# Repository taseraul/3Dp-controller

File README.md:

# 3Dp-controller
Atmega2560 compatible 3d printer controller with integrated tmc2130 stepper drivers

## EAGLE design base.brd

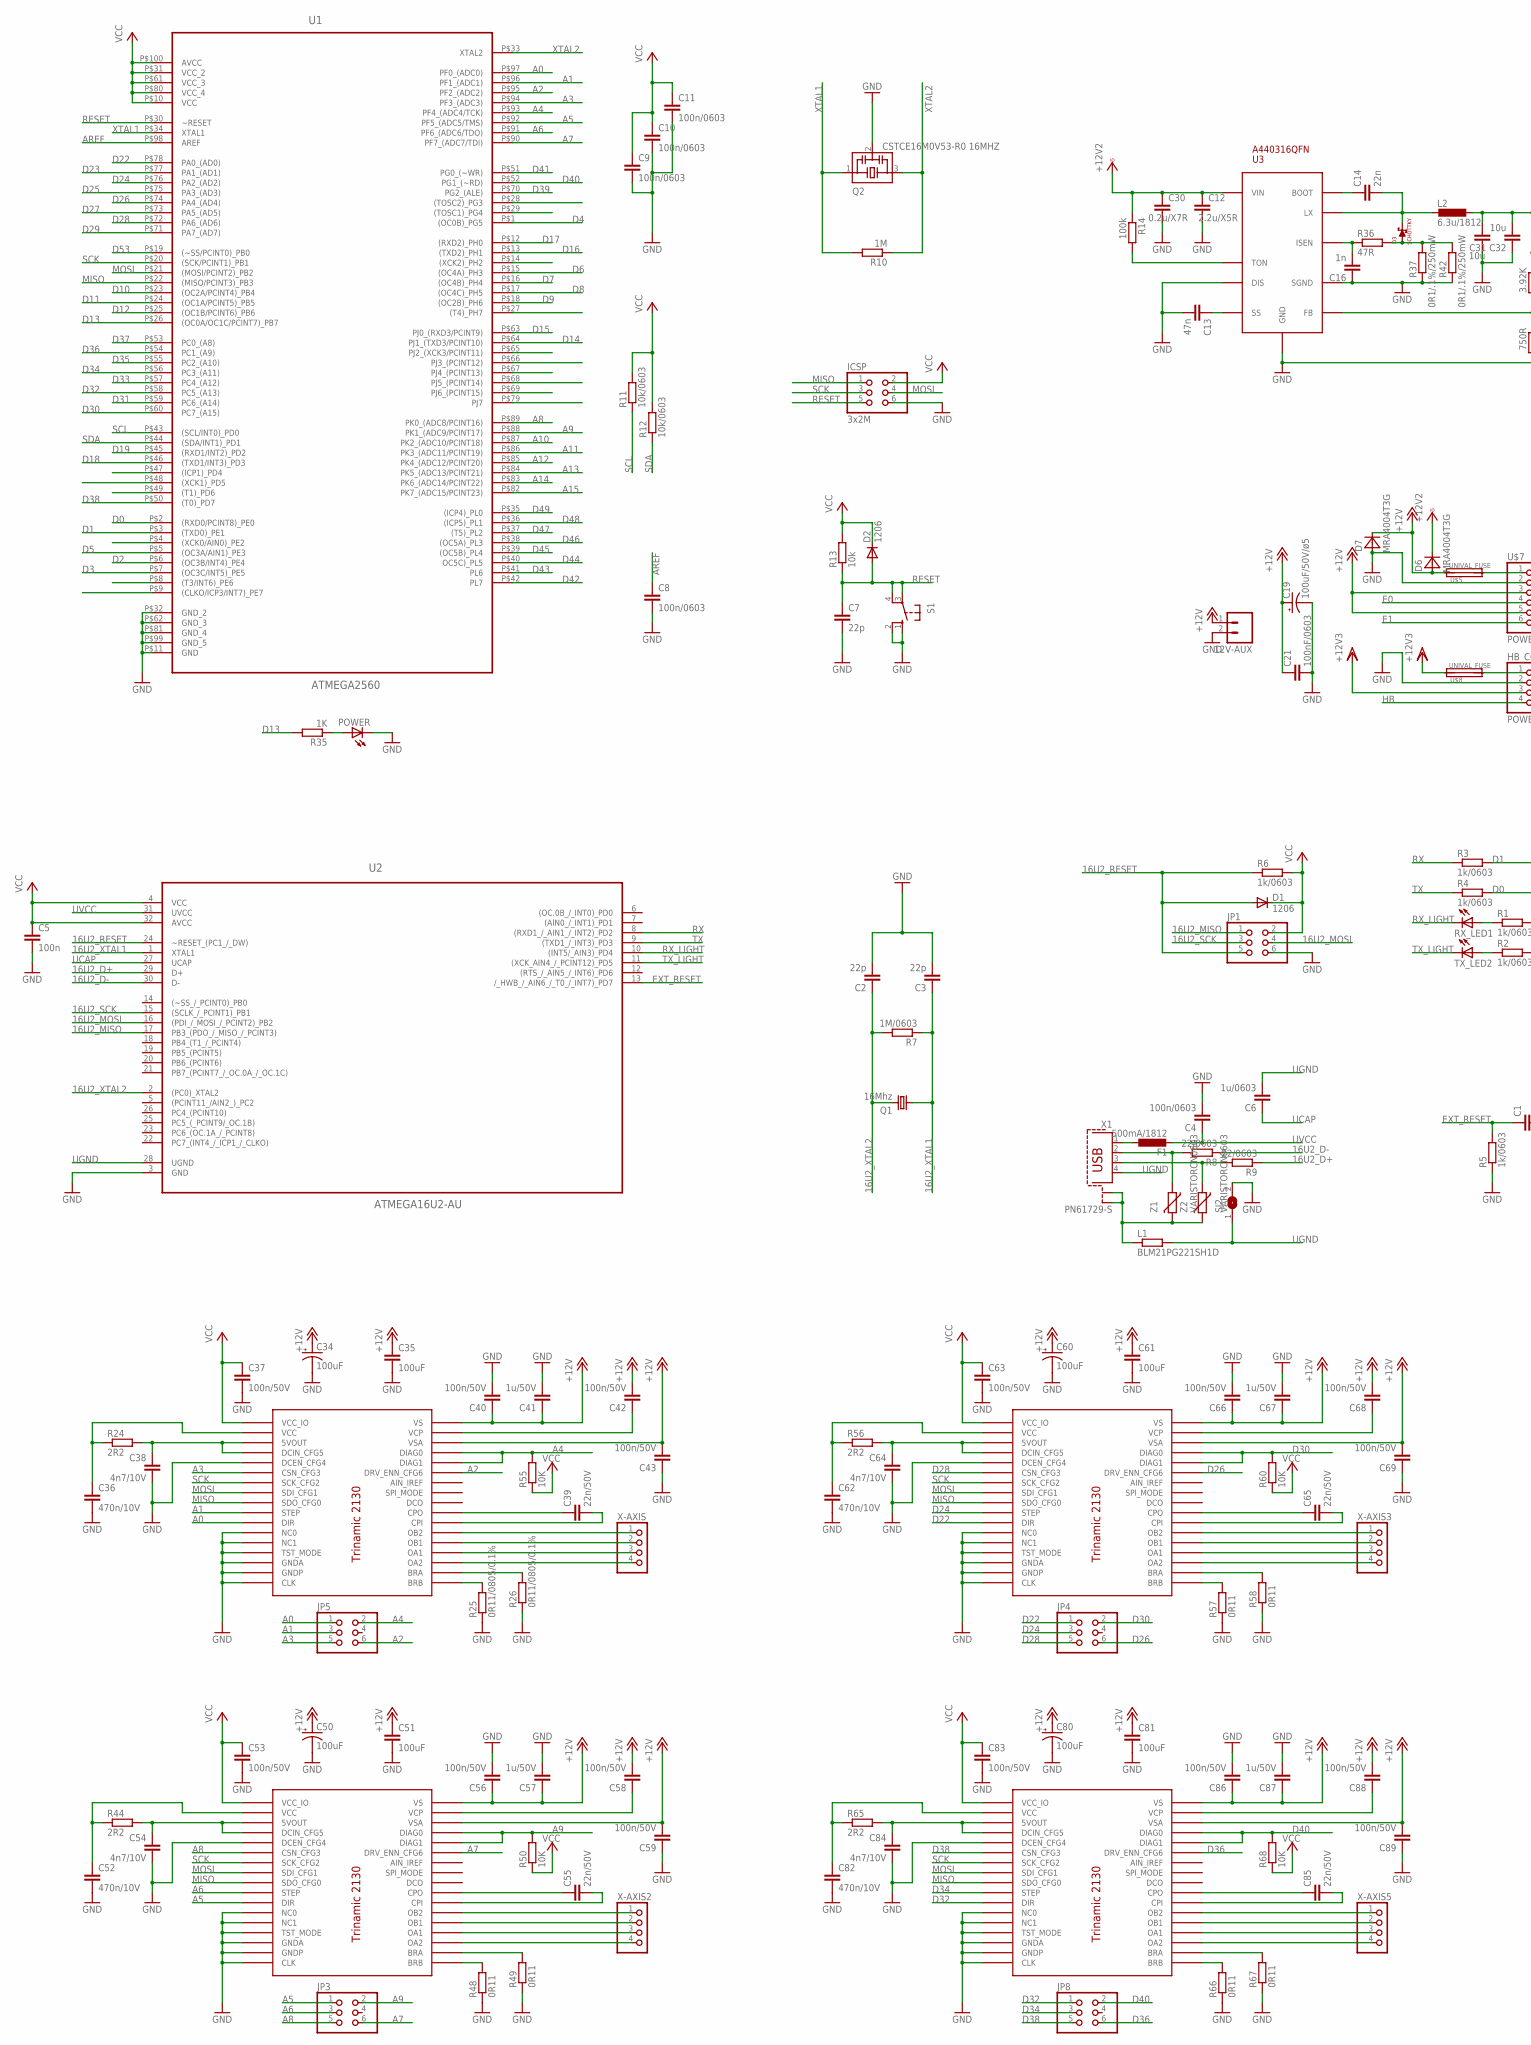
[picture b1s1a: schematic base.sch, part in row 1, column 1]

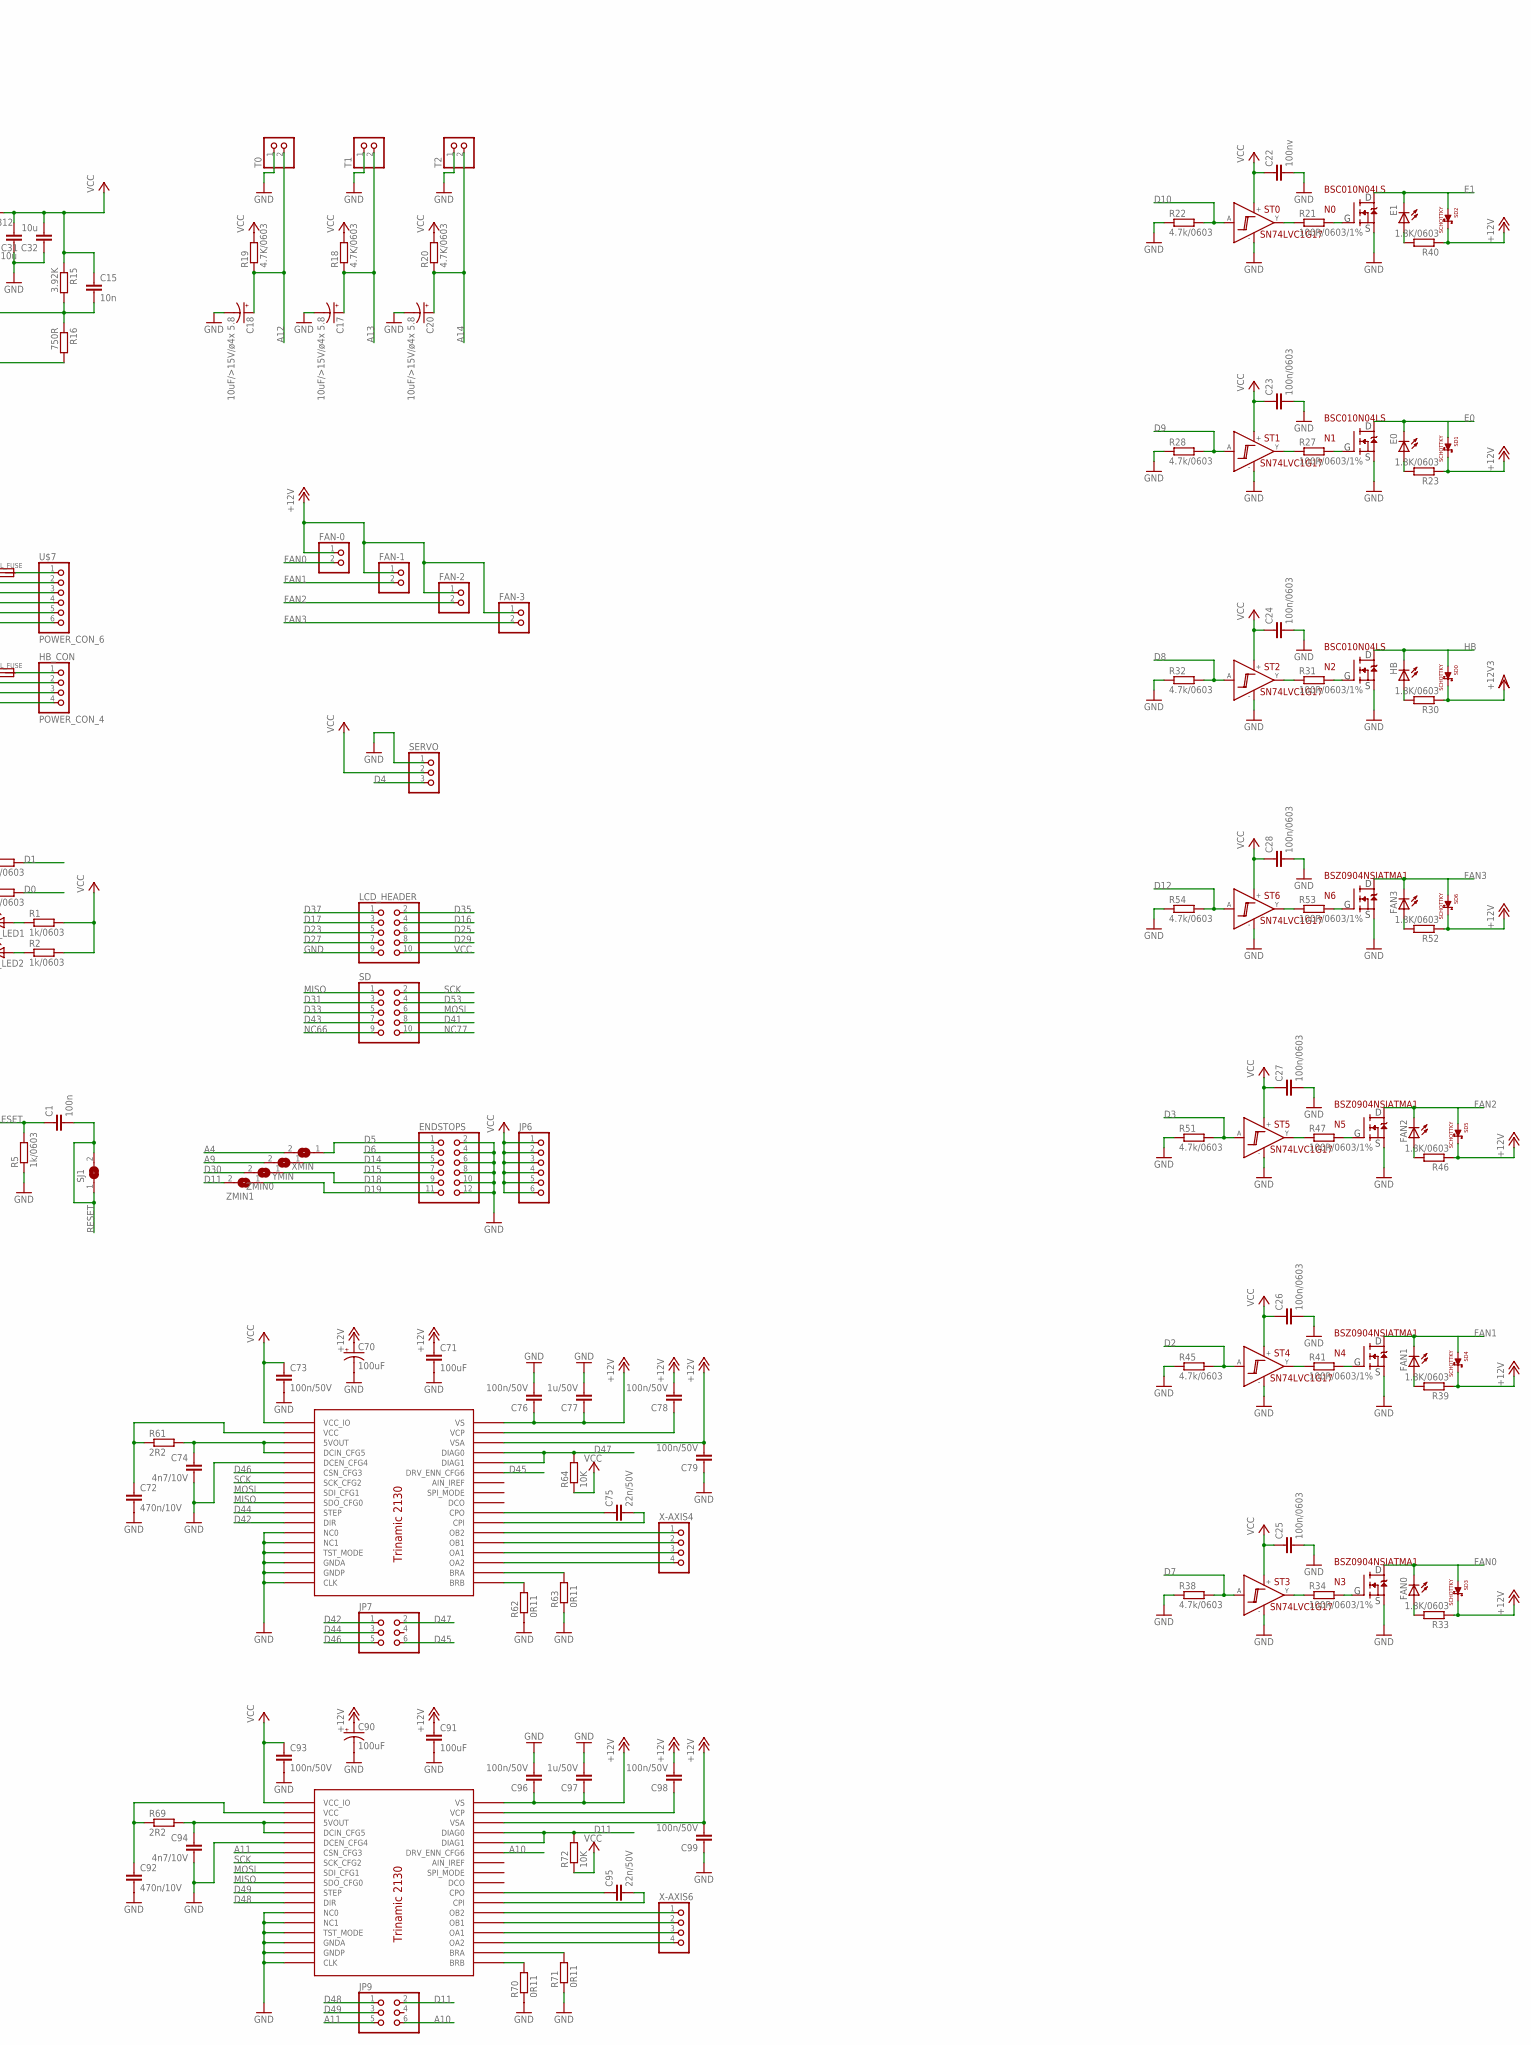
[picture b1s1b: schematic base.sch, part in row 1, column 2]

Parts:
12V-AUX: M02PTH; 1X02
C1, C5: 100n; C0603
C2, C3, C7: 22p; C0603
C4, C8, C9, C10, C11, C23, C24, C25, C26, C27, C28: 100n/0603; C0603
C6: 1u/0603; C0603
C12: 2.2u/X5R; C0805
C13: 47n; C0603
C14: 22n; C0603
C15: 10n; C0603
C16: 1n; C0603
C17, C18, C20: 10uF/>15V/ø4x 5.8; 153CLV-0405
C19: 100uF/50V/ø5; 153CLV-0605
C21: 100nF/0603; C0805
C22: 100nv; C0603
C30: 0.2u/X7R; C0603
C31, C32: 10u; C0603
C34, C50, C60, C70, C80, C90: 100uF; 153CLV-0605
C35, C51, C61, C71, C81, C91: 100uF; C0603
C36, C52, C62, C72, C82, C92: 470n/10V; C0402
C37, C40, C42, C43, C53, C56, C58, C59, C63, C66, C68, C69, C73, C76, C78, C79, C83, C86, C88, C89, C93, C96, C98, C99: 100n/50V; C0402
C38, C54, C64, C74, C84, C94: 4n7/10V; C0402
C39, C55, C65, C75, C85, C95: 22n/50V; C0402
C41, C57, C67, C77, C87, C97: 1u/50V; C0603
D1: 1206; MICROMELF-W
D2: 1206; MINIMELF
D3: SCHOTTKY; MICROSMP
D6, D7: MRA4004T3G; SMA
E0, E1: LEDCHIP-LED0805; CHIP-LED0805
ENDSTOPS: PINHD-2X6/90; 2X06/90
F1: 500mA/1812; L1812
FAN0, FAN1, FAN2, FAN3: LEDCHIP-LED0805; CHIP-LED0805
FAN-0, FAN-1, FAN-2, FAN-3: PINHD-1X2; 1X02
HB: LEDCHIP-LED0805; CHIP-LED0805
HB_CON: POWER_CON_4
ICSP: 3x2M; 2X03
JP1, JP3, JP4, JP5, JP7, JP8, JP9: PINHD-2X3; 2X03
JP6: PINHD-1X6; 1X06
L1: BLM21PG221SH1D; R0805
L2: 6.3u/1812; L1812
LCD_HEADER: PINHD-2X5; 2X05
N0, N1, N2: BSC010N04LS; TDSON-8FL
N3, N4, N5, N6: BSZ0904NSIATMA1; TSDSON-8
POWER: LEDCHIP-LED0805; CHIP-LED0805
Q1: 16Mhz; HC49/S
Q2: CSTCE16M0V53-R0 16MHZ; CSTCR6M
R1, R2, R3, R4, R5, R6: 1k/0603; R0603
R7: 1M/0603; R0603
R8, R9: 22/0603; R0603
R10: 1M; R0603
R11, R12: 10k/0603; R0603
R13: 10k; R0805
R14: 100k; R0603
R15: 3.92K; R0603
R16: 750R; R0603
R18, R19, R20: 4.7K/0603; R0603
R21, R27, R31, R34, R41, R47, R53: 100R/0603/1%; R0603
R22, R28, R32, R38, R45, R51, R54: 4.7k/0603; R0603
R23, R30, R33, R39, R40, R46, R52: 1.8K/0603; R0603
R24, R44, R56, R61, R65, R69: 2R2; R0402
R25, R26: 0R11/0805/0.1%; R0805
R35: 1K; R0603
R36: 47R; R0603
R37, R42: 0R1/.1%/250mW; R0805
R48, R49, R57, R58, R62, R63, R66, R67, R70, R71: 0R11; R0805
R50, R55, R60, R64, R68, R72: 10K; R0603
RX_LED1: LEDSML0603; SML0603
S1: 10-XX; B3F-10XX
SD: PINHD-2X5; 2X05
SD0, SD1, SD2, SD3, SD4, SD5, SD6: SCHOTTKY; MICROSMP
SERVO: PINHD-1X3/90; 1X03/90
SJ1, SJ2: SJ
ST0, ST1, ST2, ST3, ST4, ST5, ST6: SN74LVC1G17; SOT23-5
T0, T1, T2: PINHD-1X2; 1X02
TX_LED2: LEDSML0603; SML0603
U1: ATMEGA2560; 100TQFP-ATMEGA2560
U2: ATMEGA16U2-AU; QFP80P900X900X120-32N
U3: A440316QFN; 16QFN
U$2, U$3, U$4, U$6, U$9, U$10: TRINAMIC2130; 36QFN-TRINAMIC2130
U$5, U$8: UNIVAL_FUSE
U$7: POWER_CON_6
X1: PN61729-S
X-AXIS, X-AXIS2, X-AXIS3, X-AXIS4, X-AXIS5, X-AXIS6: PINHD-1X4/90; 1X04/90
XMIN: SJ
YMIN: SJ
Z1, Z2: VARISTORCN0603; CT/CN0603
ZMIN0, ZMIN1: SJ

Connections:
16U2_D+: R9.1, U2.29 (D+)
16U2_D-: R8.1, U2.30 (D-)
16U2_MISO: JP1.1, U2.17 (PB3_(PDO_/_MISO_/_PCINT3))
16U2_MOSI: JP1.4, U2.16 ((PDI_/_MOSI_/_PCINT2)_PB2)
16U2_RESET: D1.A, JP1.5, R6.1, U2.24 (~RESET_(PC1_/_DW))
16U2_SCK: JP1.3, U2.15 ((SCLK_/_PCINT1)_PB1)
16U2_XTAL1: C3.1, Q1.1, R7.1, U2.1 (XTAL1)
16U2_XTAL2: C2.1, Q1.2, R7.2, U2.2 ((PC0)_XTAL2)
+12V: 12V-AUX.1, C19.+, C21.1, C34.+, C35.1, C40.1, C41.1, C42.2, C43.2, C50.+, C51.1, C56.1, C57.1, C58.2, C59.2, C60.+, C61.1, C66.1, C67.1, C68.2, C69.2, C70.+, C71.1, C76.1, C77.1, C78.2, C79.2, C80.+, C81.1, C86.1, C87.1, C88.2, C89.2, C90.+, C91.1, C96.1, C97.1, C98.2, C99.2, D6.A, D7.C, FAN-0.1, FAN-1.1, FAN-2.1, FAN-3.1, R23.1, R33.1, R39.1, R40.1, R46.1, R52.1, SD1.P$1, SD2.P$1, SD3.P$1, SD4.P$1, SD5.P$1, SD6.P$1, U$2.VS1 (VS), U$2.VS2 (VS), U$2.VSA, U$3.VS1 (VS), U$3.VS2 (VS), U$3.VSA, U$4.VS1 (VS), U$4.VS2 (VS), U$4.VSA, U$5.P$1, U$5.P$3, U$6.VS1 (VS), U$6.VS2 (VS), U$6.VSA, U$7.3, U$7.5, U$9.VS1 (VS), U$9.VS2 (VS), U$9.VSA, U$10.VS1 (VS), U$10.VS2 (VS), U$10.VSA
A0: JP5.1, U1.P$97 (PF0_(ADC0)), U$2.DIR
A1: JP5.3, U1.P$96 (PF1_(ADC1)), U$2.STEP
A2: JP5.6, U1.P$95 (PF2_(ADC2)), U$2.DRV_ENN_CFG6
A3: JP5.5, U1.P$94 (PF3_(ADC3)), U$2.CSN_CFG3
A4: JP5.2, R55.2, U1.P$93 (PF4_(ADC4/TCK)), U$2.DIAG0, U$2.DIAG1, XMIN.2
A5: JP3.1, U1.P$92 (PF5_(ADC5/TMS)), U$4.DIR
A6: JP3.3, U1.P$91 (PF6_(ADC6/TDO)), U$4.STEP
A7: JP3.6, U1.P$90 (PF7_(ADC7/TDI)), U$4.DRV_ENN_CFG6
A8: JP3.5, U1.P$89 (PK0_(ADC8/PCINT16)), U$4.CSN_CFG3
A9: JP3.2, R50.2, U1.P$88 (PK1_(ADC9/PCINT17)), U$4.DIAG0, U$4.DIAG1, YMIN.2
A10: JP9.6, U1.P$87 (PK2_(ADC10/PCINT18)), U$10.DRV_ENN_CFG6
A11: JP9.5, U1.P$86 (PK3_(ADC11/PCINT19)), U$10.CSN_CFG3
A12: C18.+, R19.1, T0.2, U1.P$85 (PK4_(ADC12/PCINT20))
A13: C17.+, R18.1, T1.2, U1.P$84 (PK5_(ADC13/PCINT21))
A14: C20.+, R20.1, T2.2, U1.P$83 (PK6_(ADC14/PCINT22))
A15: U1.P$82 (PK7_(ADC15/PCINT23))
AREF: C8.1, U1.P$98 (AREF)
D0: R4.2, U1.P$2 ((RXD0/PCINT8)_PE0)
D1: R3.2, U1.P$3 ((TXD0)_PE1)
D2: R45.2, ST4.P$2, U1.P$6 ((OC3B/INT4)_PE4)
D3: R51.2, ST5.P$2, U1.P$7 ((OC3C/INT5)_PE5)
D4: SERVO.3, U1.P$1 ((OC0B)_PG5)
D5: ENDSTOPS.1, U1.P$5 ((OC3A/AIN1)_PE3), XMIN.1
D6: ENDSTOPS.3, U1.P$15 ((OC4A)_PH3)
D7: R38.2, ST3.P$2, U1.P$16 ((OC4B)_PH4)
D8: R32.2, ST2.P$2, U1.P$17 ((OC4C)_PH5)
D9: R28.2, ST1.P$2, U1.P$18 ((OC2B)_PH6)
D10: R22.2, ST0.P$2, U1.P$23 ((OC2A/PCINT4)_PB4)
D11: JP9.2, R72.2, U1.P$24 ((OC1A/PCINT5)_PB5), U$10.DIAG0, U$10.DIAG1, ZMIN1.2
D12: R54.2, ST6.P$2, U1.P$25 ((OC1B/PCINT6)_PB6)
D13: R35.2, U1.P$26 ((OC0A/OC1C/PCINT7)_PB7)
D14: ENDSTOPS.5, U1.P$64 (PJ1_(TXD3/PCINT10)), YMIN.1
D15: ENDSTOPS.7, U1.P$63 (PJ0_(RXD3/PCINT9))
D16: LCD_HEADER.4, U1.P$13 ((TXD2)_PH1)
D17: LCD_HEADER.3, U1.P$12 ((RXD2)_PH0)
D18: ENDSTOPS.9, U1.P$46 ((TXD1/INT3)_PD3), ZMIN0.1
D19: ENDSTOPS.11, U1.P$45 ((RXD1/INT2)_PD2), ZMIN1.1
D22: JP4.1, U1.P$78 (PA0_(AD0)), U$3.DIR
D23: LCD_HEADER.5, U1.P$77 (PA1_(AD1))
D24: JP4.3, U1.P$76 (PA2_(AD2)), U$3.STEP
D25: LCD_HEADER.6, U1.P$75 (PA3_(AD3))
D26: JP4.6, U1.P$74 (PA4_(AD4)), U$3.DRV_ENN_CFG6
D27: LCD_HEADER.7, U1.P$73 (PA5_(AD5))
D28: JP4.5, U1.P$72 (PA6_(AD6)), U$3.CSN_CFG3
D29: LCD_HEADER.8, U1.P$71 (PA7_(AD7))
D30: JP4.2, R60.2, U1.P$60 (PC7_(A15)), U$3.DIAG0, U$3.DIAG1, ZMIN0.2
D31: SD.3, U1.P$59 (PC6_(A14))
D32: JP8.1, U1.P$58 (PC5_(A13)), U$9.DIR
D33: SD.5, U1.P$57 (PC4_(A12))
D34: JP8.3, U1.P$56 (PC3_(A11)), U$9.STEP
D35: LCD_HEADER.2, U1.P$55 (PC2_(A10))
D36: JP8.6, U1.P$54 (PC1_(A9)), U$9.DRV_ENN_CFG6
D37: LCD_HEADER.1, U1.P$53 (PC0_(A8))
D38: JP8.5, U1.P$50 ((T0)_PD7), U$9.CSN_CFG3
D39: U1.P$70 (PG2_(ALE))
D40: JP8.2, R68.2, U1.P$52 (PG1_(~RD)), U$9.DIAG0, U$9.DIAG1
D41: SD.8, U1.P$51 (PG0_(~WR))
D42: JP7.1, U1.P$42 (PL7), U$6.DIR
D43: SD.7, U1.P$41 (PL6)
D44: JP7.3, U1.P$40 (OC5C)_PL5), U$6.STEP
D45: JP7.6, U1.P$39 ((OC5B)_PL4), U$6.DRV_ENN_CFG6
D46: JP7.5, U1.P$38 ((OC5A)_PL3), U$6.CSN_CFG3
D47: JP7.2, R64.2, U1.P$37 ((T5)_PL2), U$6.DIAG0, U$6.DIAG1
D48: JP9.1, U1.P$36 ((ICP5)_PL1), U$10.DIR
D49: JP9.3, U1.P$35 ((ICP4)_PL0), U$10.STEP
D53: SD.4, U1.P$19 ((~SS/PCINT0)_PB0)
E0: E0.C, N1.D, N1.P$2 (D), N1.P$3 (D), N1.P$4 (D), N1.P$5 (D), SD1.P$2, U$7.4
E1: E1.C, N0.D, N0.P$2 (D), N0.P$3 (D), N0.P$4 (D), N0.P$5 (D), SD2.P$2, U$7.6
EXT_RESET: C1.1, R5.2, U2.13 (/_HWB_/_AIN6_/_T0_/_INT7)_PD7)
FAN0: FAN0.C, FAN-0.2, N3.D, SD3.P$2
FAN1: FAN1.C, FAN-1.2, N4.D, SD4.P$2
FAN2: FAN2.C, FAN-2.2, N5.D, SD5.P$2
FAN3: FAN3.C, FAN-3.2, N6.D, SD6.P$2
GND: 12V-AUX.2, C2.2, C3.2, C4.2, C5.2, C7.2, C8.2, C9.2, C10.2, C11.2, C12.2, C13.2, C16.1, C17.-, C18.-, C19.-, C20.-, C21.2, C22.2, C23.2, C24.2, C25.2, C26.2, C27.2, C28.2, C30.2, C31.1, C32.1, C34.-, C35.2, C36.2, C37.2, C38.2, C40.2, C41.2, C43.1, C50.-, C51.2, C52.2, C53.2, C54.2, C56.2, C57.2, C59.1, C60.-, C61.2, C62.2, C63.2, C64.2, C66.2, C67.2, C69.1, C70.-, C71.2, C72.2, C73.2, C74.2, C76.2, C77.2, C79.1, C80.-, C81.2, C82.2, C83.2, C84.2, C86.2, C87.2, C89.1, C90.-, C91.2, C92.2, C93.2, C94.2, C96.2, C97.2, C99.1, D7.A, ENDSTOPS.2, ENDSTOPS.4, ENDSTOPS.6, ENDSTOPS.8, ENDSTOPS.10, ENDSTOPS.12, HB_CON.2, ICSP.6, JP1.6, LCD_HEADER.9, N0.S, N1.S, N2.S, N3.S, N4.S, N5.S, N6.S, POWER.C, Q2.2, R5.1, R16.2, R22.1, R25.1, R26.1, R28.1, R32.1, R37.1, R38.1, R42.1, R45.1, R48.1, R49.1, R51.1, R54.1, R57.1, R58.1, R62.1, R63.1, R66.1, R67.1, R70.1, R71.1, S1.1 (S), S1.2 (S1), SERVO.1, SJ2.2, ST0.P$3, ST1.P$3, ST2.P$3, ST3.P$3, ST4.P$3, ST5.P$3, ST6.P$3, T0.1, T1.1, T2.1, U1.P$11 (GND), U1.P$32 (GND_2), U1.P$62 (GND_3), U1.P$81 (GND_4), U1.P$99 (GND_5), U2.3 (GND), U3.2 (GND), U3.7 (GND), U3.13 (GND), U3.14 (GND), U3.15 (GND), U3.16 (GND), U3.DIS, U3.GND, U3.PAD (GND), U3.SGND, U$2.- (NC0), U$2.CLK, U$2.DCEN_CFG4, U$2.GND (GNDA), U$2.GNDA, U$2.GNDP1 (GNDP), U$2.GNDP2 (GNDP), U$2.NC2 (NC1), U$2.P$37 (GNDA), U$2.P$38 (GNDA), U$2.P$39 (GNDA), U$2.P$40 (GNDA), U$2.P$41 (GNDA), U$2.P$42 (GNDA), U$2.P$43 (GNDA), U$2.P$44 (GNDA), U$2.P$45 (GNDA), U$2.P$46 (GNDA), U$2.P$47 (GNDA), U$2.P$48 (GNDA), U$2.P$49 (GNDA), U$2.P$50 (GNDA), U$2.P$51 (GNDA), U$2.P$52 (GNDA), U$2.TST_MODE, U$3.- (NC0), U$3.CLK, U$3.DCEN_CFG4, U$3.GND (GNDA), U$3.GNDA, U$3.GNDP1 (GNDP), U$3.GNDP2 (GNDP), U$3.NC2 (NC1), U$3.P$37 (GNDA), U$3.P$38 (GNDA), U$3.P$39 (GNDA), U$3.P$40 (GNDA), U$3.P$41 (GNDA), U$3.P$42 (GNDA), U$3.P$43 (GNDA), U$3.P$44 (GNDA), U$3.P$45 (GNDA), U$3.P$46 (GNDA), U$3.P$47 (GNDA), U$3.P$48 (GNDA), U$3.P$49 (GNDA), U$3.P$50 (GNDA), U$3.P$51 (GNDA), U$3.P$52 (GNDA), U$3.TST_MODE, U$4.- (NC0), U$4.CLK, U$4.DCEN_CFG4, U$4.GND (GNDA), U$4.GNDA, U$4.GNDP1 (GNDP), U$4.GNDP2 (GNDP), U$4.NC2 (NC1), U$4.P$37 (GNDA), U$4.P$38 (GNDA), U$4.P$39 (GNDA), U$4.P$40 (GNDA), U$4.P$41 (GNDA), U$4.P$42 (GNDA), U$4.P$43 (GNDA), U$4.P$44 (GNDA), U$4.P$45 (GNDA), U$4.P$46 (GNDA), U$4.P$47 (GNDA), U$4.P$48 (GNDA), U$4.P$49 (GNDA), U$4.P$50 (GNDA), U$4.P$51 (GNDA), U$4.P$52 (GNDA), U$4.TST_MODE, U$6.- (NC0), U$6.CLK, U$6.DCEN_CFG4, U$6.GND (GNDA), U$6.GNDA, U$6.GNDP1 (GNDP), U$6.GNDP2 (GNDP), U$6.NC2 (NC1), U$6.P$37 (GNDA), U$6.P$38 (GNDA), U$6.P$39 (GNDA), U$6.P$40 (GNDA), U$6.P$41 (GNDA), U$6.P$42 (GNDA), U$6.P$43 (GNDA), U$6.P$44 (GNDA), U$6.P$45 (GNDA), U$6.P$46 (GNDA), U$6.P$47 (GNDA), U$6.P$48 (GNDA), U$6.P$49 (GNDA), U$6.P$50 (GNDA), U$6.P$51 (GNDA), U$6.P$52 (GNDA), U$6.TST_MODE, U$7.2, U$9.- (NC0), U$9.CLK, U$9.DCEN_CFG4, U$9.GND (GNDA), U$9.GNDA, U$9.GNDP1 (GNDP), U$9.GNDP2 (GNDP), U$9.NC2 (NC1), U$9.P$37 (GNDA), U$9.P$38 (GNDA), U$9.P$39 (GNDA), U$9.P$40 (GNDA), U$9.P$41 (GNDA), U$9.P$42 (GNDA), U$9.P$43 (GNDA), U$9.P$44 (GNDA), U$9.P$45 (GNDA), U$9.P$46 (GNDA), U$9.P$47 (GNDA), U$9.P$48 (GNDA), U$9.P$49 (GNDA), U$9.P$50 (GNDA), U$9.P$51 (GNDA), U$9.P$52 (GNDA), U$9.TST_MODE, U$10.- (NC0), U$10.CLK, U$10.DCEN_CFG4, U$10.GND (GNDA), U$10.GNDA, U$10.GNDP1 (GNDP), U$10.GNDP2 (GNDP), U$10.NC2 (NC1), U$10.P$37 (GNDA), U$10.P$38 (GNDA), U$10.P$39 (GNDA), U$10.P$40 (GNDA), U$10.P$41 (GNDA), U$10.P$42 (GNDA), U$10.P$43 (GNDA), U$10.P$44 (GNDA), U$10.P$45 (GNDA), U$10.P$46 (GNDA), U$10.P$47 (GNDA), U$10.P$48 (GNDA), U$10.P$49 (GNDA), U$10.P$50 (GNDA), U$10.P$51 (GNDA), U$10.P$52 (GNDA), U$10.TST_MODE
HB: HB.C, HB_CON.4, N2.D, N2.P$2 (D), N2.P$3 (D), N2.P$4 (D), N2.P$5 (D), SD0.P$2
MISO: ICSP.1, SD.1, U1.P$22 ((MISO/PCINT3)_PB3), U$2.SDO_CFG0, U$3.SDO_CFG0, U$4.SDO_CFG0, U$6.SDO_CFG0, U$9.SDO_CFG0, U$10.SDO_CFG0
MOSI: ICSP.4, SD.6, U1.P$21 ((MOSI/PCINT2)_PB2), U$2.SDI_CFG1, U$3.SDI_CFG1, U$4.SDI_CFG1, U$6.SDI_CFG1, U$9.SDI_CFG1, U$10.SDI_CFG1
unnamed: R8.2, X1.2, Z1.1
unnamed: R1.1, RX_LED1.A
unnamed: R9.2, X1.3, Z2.1
unnamed: R2.1, TX_LED2.A
unnamed: F1.1, X1.1
unnamed: L1.1, X1.S1, X1.S2, Z1.2, Z2.2
unnamed: R14.2, U3.TON
unnamed: C14.1, U3.BOOT
unnamed: N3.G, R34.2
unnamed: HB_CON.1, U$8.P$2, U$8.P$4
unnamed: C14.2, D3.P$1, L2.2, U3.LX
unnamed: U$5.P$2, U$5.P$4, U$7.1
unnamed: C13.1, U3.SS
unnamed: POWER.A, R35.1
unnamed: R21.1, ST0.P$4
unnamed: N1.G, R27.2
unnamed: E0.A, R23.2
unnamed: R27.1, ST1.P$4
unnamed: N2.G, R31.2
unnamed: D3.P$2, R36.2, R37.2, R42.2
unnamed: C16.2, R36.1, U3.ISEN
unnamed: HB.A, R30.2
unnamed: R31.1, ST2.P$4
unnamed: FAN0.A, R33.2
unnamed: R34.1, ST3.P$4
unnamed: N4.G, R41.2
unnamed: FAN1.A, R39.2
unnamed: R41.1, ST4.P$4
unnamed: N5.G, R47.2
unnamed: C38.1, R24.2, U$2.5VOUT, U$2.DCIN_CFG5
unnamed: C36.1, R24.1, U$2.VCC
unnamed: U$2.OB2, X-AXIS.1
unnamed: R25.2, U$2.BRB
unnamed: R26.2, U$2.BRA
unnamed: C39.1, U$2.CPO
unnamed: C39.2, U$2.CPI
unnamed: C42.1, U$2.VCP
unnamed: U$2.OB1, X-AXIS.2
unnamed: U$2.OA1, X-AXIS.3
unnamed: U$2.OA2, X-AXIS.4
unnamed: FAN2.A, R46.2
unnamed: R47.1, ST5.P$4
unnamed: N6.G, R53.2
unnamed: FAN3.A, R52.2
unnamed: C15.2, R15.2, R16.1, U3.FB
unnamed: C54.1, R44.2, U$4.5VOUT, U$4.DCIN_CFG5
unnamed: C52.1, R44.1, U$4.VCC
unnamed: U$4.OB2, X-AXIS2.1
unnamed: R48.2, U$4.BRB
unnamed: R53.1, ST6.P$4
unnamed: R49.2, U$4.BRA
unnamed: C55.1, U$4.CPO
unnamed: C55.2, U$4.CPI
unnamed: N0.G, R21.2
unnamed: E1.A, R40.2
unnamed: C58.1, U$4.VCP
unnamed: U$4.OB1, X-AXIS2.2
unnamed: U$4.OA1, X-AXIS2.3
unnamed: U$4.OA2, X-AXIS2.4
unnamed: C64.1, R56.2, U$3.5VOUT, U$3.DCIN_CFG5
unnamed: C62.1, R56.1, U$3.VCC
unnamed: U$3.OB2, X-AXIS3.1
unnamed: R57.2, U$3.BRB
unnamed: R58.2, U$3.BRA
unnamed: C65.1, U$3.CPO
unnamed: C65.2, U$3.CPI
unnamed: C68.1, U$3.VCP
unnamed: U$3.OB1, X-AXIS3.2
unnamed: U$3.OA1, X-AXIS3.3
unnamed: U$3.OA2, X-AXIS3.4
unnamed: C74.1, R61.2, U$6.5VOUT, U$6.DCIN_CFG5
unnamed: C72.1, R61.1, U$6.VCC
unnamed: U$6.OB2, X-AXIS4.1
unnamed: R62.2, U$6.BRB
unnamed: R63.2, U$6.BRA
unnamed: C75.1, U$6.CPO
unnamed: C75.2, U$6.CPI
unnamed: C78.1, U$6.VCP
unnamed: U$6.OB1, X-AXIS4.2
unnamed: U$6.OA1, X-AXIS4.3
unnamed: U$6.OA2, X-AXIS4.4
unnamed: C84.1, R65.2, U$9.5VOUT, U$9.DCIN_CFG5
unnamed: C82.1, R65.1, U$9.VCC
unnamed: U$9.OB2, X-AXIS5.1
unnamed: R66.2, U$9.BRB
unnamed: R67.2, U$9.BRA
unnamed: C85.1, U$9.CPO
unnamed: C85.2, U$9.CPI
unnamed: C88.1, U$9.VCP
unnamed: U$9.OB1, X-AXIS5.2
unnamed: U$9.OA1, X-AXIS5.3
unnamed: U$9.OA2, X-AXIS5.4
unnamed: C94.1, R69.2, U$10.5VOUT, U$10.DCIN_CFG5
unnamed: C92.1, R69.1, U$10.VCC
unnamed: U$10.OB2, X-AXIS6.1
unnamed: R70.2, U$10.BRB
unnamed: R71.2, U$10.BRA
unnamed: C95.1, U$10.CPO
unnamed: C95.2, U$10.CPI
unnamed: C98.1, U$10.VCP
unnamed: U$10.OB1, X-AXIS6.2
unnamed: U$10.OA1, X-AXIS6.3
unnamed: U$10.OA2, X-AXIS6.4
NC66: SD.9
NC77: SD.10
RESET: C1.2, C7.1, D2.A, ICSP.5, R13.1, S1.3, S1.4 (P1), SJ1.1, SJ1.2, U1.P$30 (~RESET)
RX: R3.1, U2.8 ((RXD1_/_AIN1_/_INT2)_PD2)
RX_LIGHT: RX_LED1.C, U2.10 ((INT5/_AIN3)_PD4)
SCK: ICSP.3, SD.2, U1.P$20 ((SCK/PCINT1)_PB1), U$2.SCK_CFG2, U$3.SCK_CFG2, U$4.SCK_CFG2, U$6.SCK_CFG2, U$9.SCK_CFG2, U$10.SCK_CFG2
SCL: R11.1, U1.P$43 ((SCL/INT0)_PD0)
SDA: R12.1, U1.P$44 ((SDA/INT1)_PD1)
TX: R4.1, U2.9 ((TXD1_/_INT3)_PD3)
TX_LIGHT: TX_LED2.C, U2.11 ((XCK_AIN4_/_PCINT12)_PD5)
UCAP: C6.1, U2.27 (UCAP)
UGND: C6.2, L1.2, SJ2.1, U2.28 (UGND), X1.4
UVCC: C4.1, F1.2, U2.31 (UVCC)
VCC: C5.1, C9.1, C10.1, C11.1, C15.1, C22.1, C23.1, C24.1, C25.1, C26.1, C27.1, C28.1, C31.2, C32.2, C37.1, C53.1, C63.1, C73.1, C83.1, C93.1, D1.C, D2.C, ICSP.2, JP1.2, JP6.1, JP6.2, JP6.3, JP6.4, JP6.5, JP6.6, L2.1, LCD_HEADER.10, R1.2, R2.2, R6.2, R11.2, R12.2, R13.2, R15.1, R18.2, R19.2, R20.2, R50.1, R55.1, R60.1, R64.1, R68.1, R72.1, SERVO.2, ST0.P$5, ST1.P$5, ST2.P$5, ST3.P$5, ST4.P$5, ST5.P$5, ST6.P$5, U1.P$10 (VCC), U1.P$31 (VCC_2), U1.P$61 (VCC_3), U1.P$80 (VCC_4), U1.P$100 (AVCC), U2.4 (VCC), U2.32 (AVCC), U$2.VCC_IO, U$3.VCC_IO, U$4.VCC_IO, U$6.VCC_IO, U$9.VCC_IO, U$10.VCC_IO
VCCIO: C12.1, C30.1, D6.C, R14.1, U3.VIN
VDD: HB_CON.3, R30.1, SD0.P$1, U$8.P$1, U$8.P$3
XTAL1: Q2.1, R10.2, U1.P$34 (XTAL1)
XTAL2: Q2.3, R10.1, U1.P$33 (XTAL2)

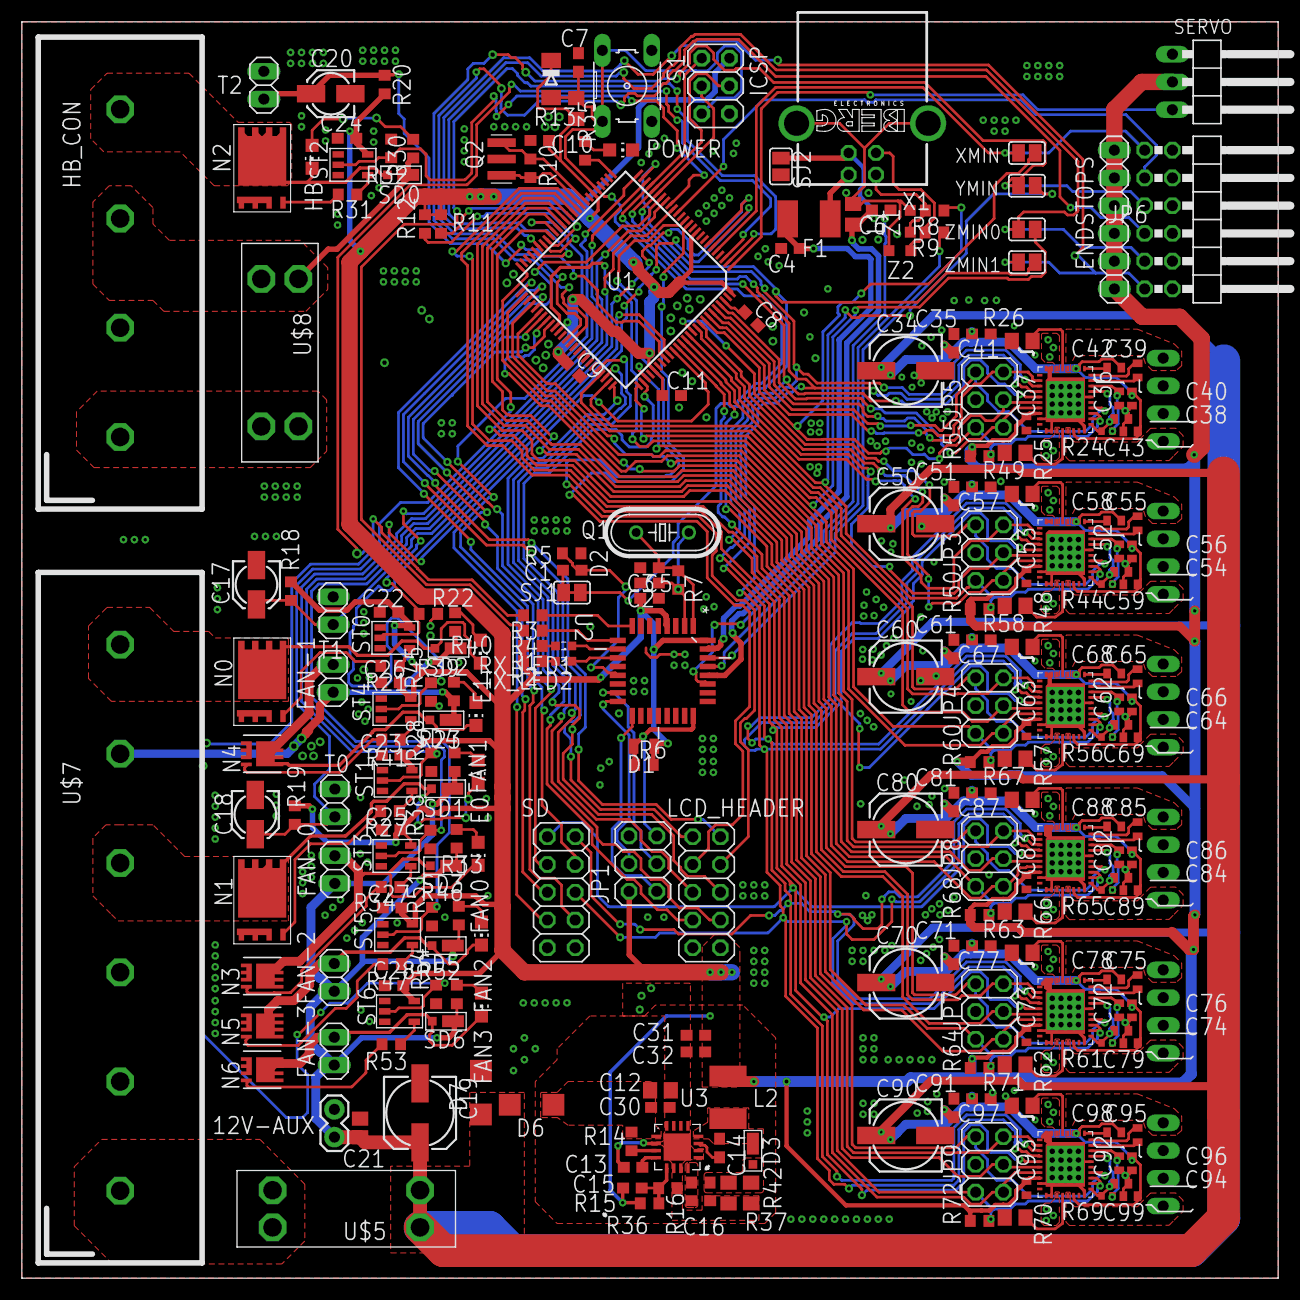
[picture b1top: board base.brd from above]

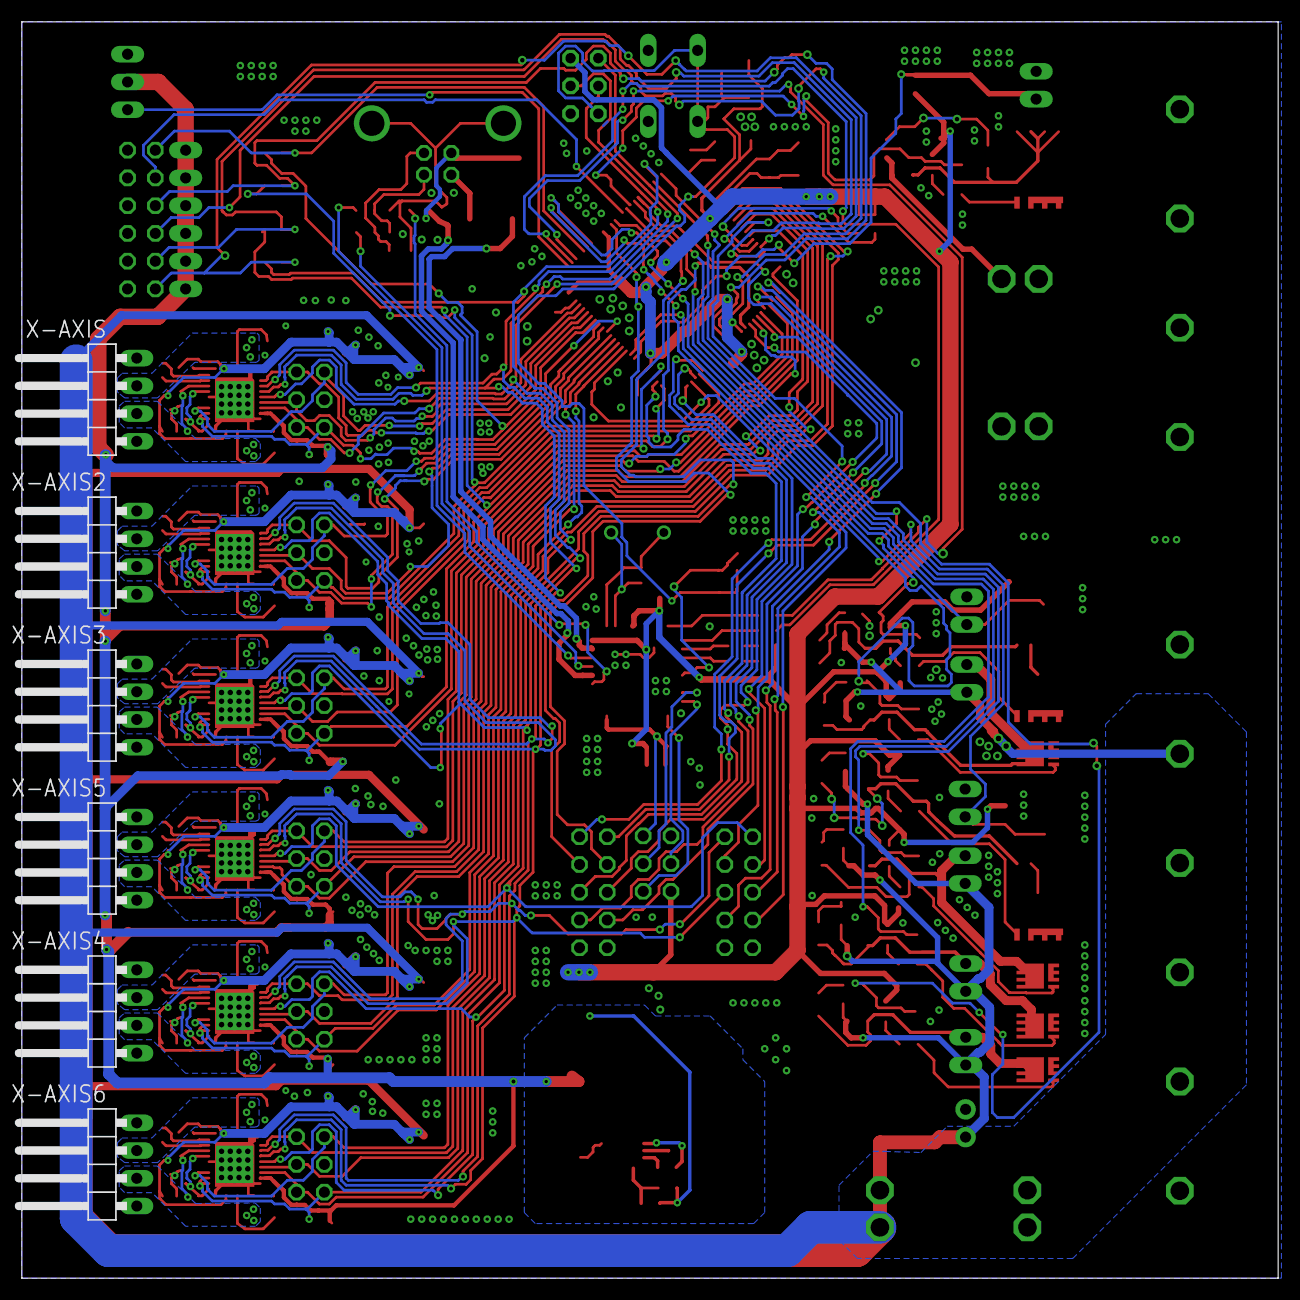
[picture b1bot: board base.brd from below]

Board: 2 copper layers, 115.0 x 115.0 mm, 250 parts (6 on the bottom side), 203 nets.
